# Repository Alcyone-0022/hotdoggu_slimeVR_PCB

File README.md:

# hotdoggu_slimeVR_PCB
KiCad project - slimevr tracker using Geekble mini ESP32C3, MPU6050    
Includes PCB Antenna (Meandered PIFA 2.4Ghz)    
&nbsp;&nbsp;&nbsp;&nbsp;&nbsp;***Solder 1st pin(left side pin of ant. from top view) to Geekble mini's Ant feed(right side pad from top view)***    
Includes 3d-printable case **(for 18650 cell and socket, needs glue like hot melt for assembly)**
# Used Components
|Component|Description|Link|
|---------|-----------|----|
|Geekble Mini ESP32C3|ESP32C3 module|https://www.devicemart.co.kr/goods/view?no=15483281|
|GY-521|MPU6050 module|https://www.devicemart.co.kr/goods/view?no=1247052|
|MSL-1C2P|Power Switch|https://www.devicemart.co.kr/goods/view?no=38883|
|100k axial resistor|2ea. For battery voltage measurement|-|
|18650 Li-ion cell|1ea. use any 18650 cell or Li-ion battery. Solder to J2.    Note:    the 3d model in STL files is made for 18650 cell. **This PCB does NOT has charging circuit!**|-|
|BB521|18650 battery socket|https://www.devicemart.co.kr/goods/view?no=12766763|
|26AWG Cable|Connect main to aux IMU. Use or make twisted pair of VCC-SDA/GND-SCK. <a href="https://docs.slimevr.dev/diy/tracker-schematics.html">See slimeVR Documentation</a>|-|
# slimeVR Configuration
**platformio.ini**
```ini
[env:esp32c3]
platform = espressif32 @ 6.7.0
platform_packages =
 framework-arduinoespressif32 @ https://github.com/espressif/arduino-esp32.git#3.0.1
 framework-arduinoespressif32-libs @ https://github.com/espressif/arduino-esp32/releases/download/3.0.1/esp32-arduino-libs-3.0.1.zip
build_flags =
 ${env.build_flags}
 -DESP32C3
board = lolin_c3_mini
```
    
**defines.h**
```C
#define IMU IMU_MPU6050
#define SECOND_IMU IMU_MPU6050
#define BOARD BOARD_CUSTOM
#define IMU_ROTATION DEG_270
#define SECOND_IMU_ROTATION DEG_180
#define PRIMARY_IMU_OPTIONAL false
#define SECONDARY_IMU_OPTIONAL true
#define MAX_IMU_COUNT 2
#ifndef IMU_DESC_LIST
#define IMU_DESC_LIST \
    IMU_DESC_ENTRY(IMU,        PRIMARY_IMU_ADDRESS_ONE,   IMU_ROTATION,        PIN_IMU_SCL, PIN_IMU_SDA, PRIMARY_IMU_OPTIONAL, PIN_IMU_INT) \
    IMU_DESC_ENTRY(SECOND_IMU, SECONDARY_IMU_ADDRESS_TWO, SECOND_IMU_ROTATION, PIN_IMU_SCL, PIN_IMU_SDA, SECONDARY_IMU_OPTIONAL, PIN_IMU_INT_2)
#endif
#define BATTERY_MONITOR BAT_EXTERNAL
#elif BOARD == BOARD_CUSTOM
#define LED_PIN 10
#define LED_INVERTED false
#define PIN_IMU_SDA 3
#define PIN_IMU_SCL 4
#define PIN_IMU_INT 255
#define PIN_IMU_INT_2 255
#define PIN_BATTERY_LEVEL 0
#define BATTERY_SHIELD_RESISTANCE 0
#define BATTERY_SHIELD_R1 100
#define BATTERY_SHIELD_R2 100
```

# Thanks to
SooDragon - the maker of Geekble Mini   
https://github.com/SooDragon/GeekbleMini-ESP32C3.git    
usini - usini_kicad_sensors    
https://github.com/usini/usini_kicad_sensors

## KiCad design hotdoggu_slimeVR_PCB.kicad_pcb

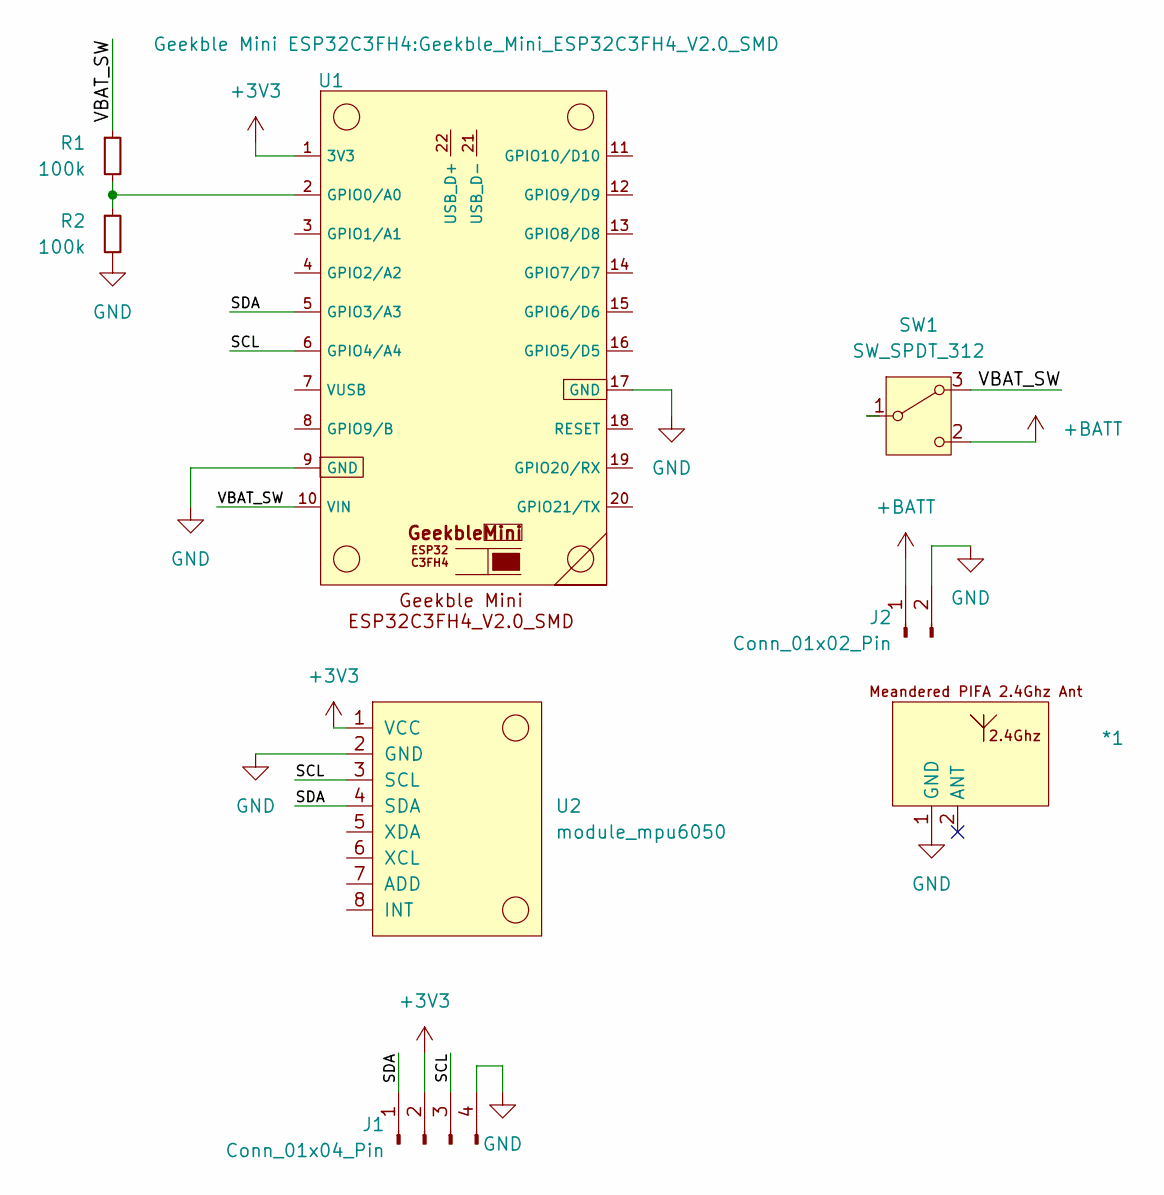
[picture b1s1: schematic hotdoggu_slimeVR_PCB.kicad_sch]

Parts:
*1: Meandered PIFA 2.4Ghz Ant
J1: Conn_01x04_Pin; SolderWire-0.5sqmm_1x04_P4.6mm_D0.9mm_OD2.1mm
J2: Conn_01x02_Pin; SolderWire-0.5sqmm_1x02_P4.8mm_D0.9mm_OD2.3mm
R1, R2: 100k; R_Axial_DIN0204_L3.6mm_D1.6mm_P7.62mm_Horizontal
SW1: SW_SPDT_312; MSL_1C2P
U1: Geekble_Mini_ESP32C3FH4_V2.0_SMD
U2: module_mpu6050

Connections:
+3V3: J1.2, U1.1 (3V3), U2.1 (VCC)
+BATT: J2.1, SW1.2 (C)
/SCL: J1.3, U1.6 (GPIO4/A4), U2.3 (SCL)
/SDA: J1.1, U1.5 (GPIO3/A3), U2.4 (SDA)
/VBAT_SW: R1.1, SW1.3 (A), U1.10 (VIN)
GND: *1.1 (GND), J1.4, J2.2, R2.2, U1.9 (GND), U1.17 (GND), U2.2 (GND)
unnamed: R1.2, R2.1, U1.2 (GPIO0/A0)

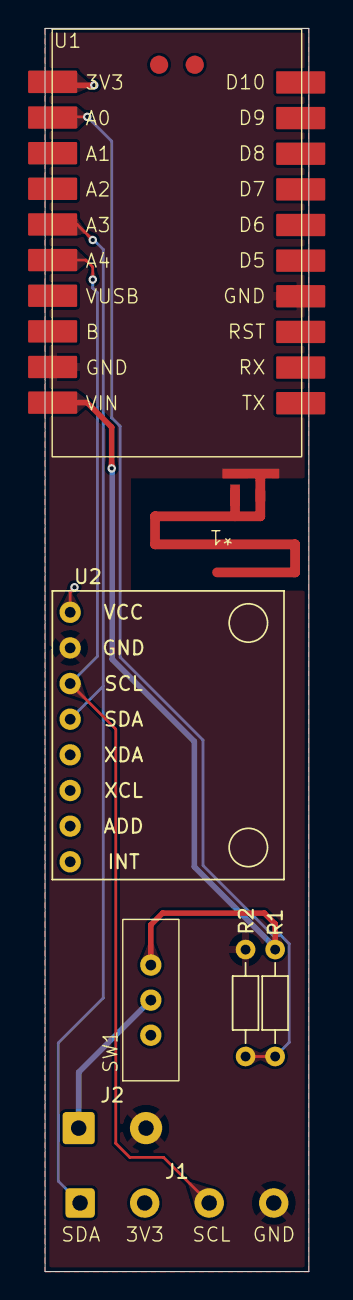
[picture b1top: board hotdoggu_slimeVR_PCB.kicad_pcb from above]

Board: 2 copper layers, 18.8 x 88.6 mm, 8 parts (0 on the bottom side), 7 nets.

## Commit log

2025-02-18 initial commit, PCB Rev v2
2025-02-18 add housing STL files
2025-02-18 some line changes
2025-02-18 add README.md
2025-02-18 modify README.md
2025-02-26 resize img
2025-02-27 pattern, sym, footprint update
2025-02-28 seperate sym, lib / update routing
2025-03-09 changes for GeekbleMini V2.0
